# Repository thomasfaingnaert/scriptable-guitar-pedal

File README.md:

# A scriptable guitar pedal

## Building
### GNU/Linux (native compilation)
The following instructions are for Debian-based distributions.
Change the commands according to the distribution you are using.

1. Install the following prerequisites:
  - CMake
  - GNU Toolchain
  - Make
```bash
sudo apt-get update
sudo apt-get upgrade
sudo apt-get install cmake build-essential
```

2. Clone the repository and build the project:
```bash
git clone https://github.com/thomasfaingnaert/scriptable-guitar-pedal
mkdir build
cd build
cmake ../scriptable-guitar-pedal
make
```

3. Run the executable:
```bash
chmod +x ./scriptable-guitar-pedal
./scriptable-guitar-pedal
```

### Windows (cross compilation)
1. Install the following prerequisites, and make sure they are in your PATH:
  - CMake (https://cmake.org/)
  - Beaglebone GNU Toolchain (http://gnutoolchains.com/beaglebone/)
  - NMake (included in Visual Studio or Microsoft Visual C++ Build Tools)
  - PuTTY (https://www.putty.org/)

2. Clone the repository and build the project:
```powershell
git clone https://github.com/thomasfaingnaert/scriptable-guitar-pedal
mkdir build
cd build
cmake -G"NMake Makefiles" -DCMAKE_TOOLCHAIN_FILE="../scriptable-guitar-pedal/cmake/Toolchain.cmake" ../scriptable-guitar-pedal
nmake
```

### GNU/Linux (cross compilation)
1. Install the following prerequisites:
  - CMake
  - GNU Toolchain for ARM
  - Make

If you are using Ubuntu or one of its derivatives:
```bash
sudo apt install make cmake binutils-arm-linux-gnueabihf gcc-arm-linux-gnueabihf g++-arm-linux-gnueabihf
```

If you are using Fedora:
```bash
sudo dnf copr enable lantw44/arm-linux-gnueabihf-toolchain
sudo dnf install make cmake arm-linux-gnueabihf-{binutils,gcc,glibc}
```

Otherwise, change the commands according to the distribution you are using.

2. Clone the repository and build the project:
```bash
git clone https://github.com/thomasfaingnaert/scriptable-guitar-pedal
mkdir build
cd build
cmake -DCMAKE_TOOLCHAIN_FILE="../scriptable-guitar-pedal/cmake/Toolchain.cmake" ../scriptable-guitar-pedal
make
```

## Configuring the PRU
These instructions are for the Beaglebone image [Debian 9.3 2018-03-05 4GB SD IoT](http://debian.beagleboard.org/images/bone-debian-9.3-iot-armhf-2018-03-05-4gb.img.xz).
They may or may not work for you if you use a different one.

1. Make sure you can access the internet on the BeagleBone Black.
This can be done by configuring your internet adapter on your PC to share its connection with the Beaglebone.
Create a script `internet.sh` with the following contents:
```bash
#!/usr/bin/env bash
route add default gw 192.168.7.1
echo "nameserver 8.8.8.8" >> /etc/resolv.conf
```
Finally, run the script with sudo:
```bash
chmod +x ./internet.sh
sudo ./internet.sh
```

2. Update all packages:
```bash
sudo apt update
sudo apt upgrade
```

3. Delete RoboticsCape, as it blacklists the `uio_pruss` module
```bash
sudo apt purge roboticscape
```

4. Apply the Xenomai patches to the kernel using:
```bash
cd /opt/scripts/tools/
git pull
sudo ./update_kernel.sh --ti-xenomai-kernel --lts-4_9
sudo reboot
```
Finally, you can check if you are running the right kernel using:
```bash
uname -a
```
This should output something similar to `Linux beaglebone 4.9.88-ti-xenomai-r107 #1 SMP PREEMPT Sat Mar 24 09:29:27 UTC 2018 armv7l GNU/Linux`.

5. Next, we need to install our custom overlay:
```bash
cd device-tree/
make
sudo make install
```

6. Enable it by copying `uEnv-pru.txt` to the `boot/` folder:
```bash
cd boot/
sudo cp uEnv-pru.txt /boot/uEnv.txt
```

7. The UIO driver should now be loaded. You can verify this by running:
```bash
lsmod | grep uio
ls /dev/uio*
```

8. If you want to assemble PRU Assembly files on your PC, you should install the PRU assembler from https://github.com/beagleboard/am335x_pru_package.
Otherwise, you could copy the `*.p` files to the BBB using SCP and assemble them there.
To assemble a file `test.p`, you can use:
```bash
pasm -b test.p
```

9. Install the RTDM kernel module from https://github.com/thomasfaingnaert/rtdm_pruss_irq:
```bash
wget https://github.com/thomasfaingnaert/rtdm_pruss_irq/releases/download/v1.0/rtdm_pruss_irq.ko
sudo cp rtdm_pruss_irq.ko /lib/modules/`uname -r`/extra
sudo depmod -a
sudo modprobe rtdm_pruss_irq
```

10. Run the PRU loader to execute the PRU code:
```bash
./scriptable-guitar-pedal test.bin
```

## Building the ASoC codec driver

### GNU/Linux - Fedora (cross compilation)
These instructions are for Fedora based distributions.
Change the commands according to the distribution you are using.

1. Clone the official BeagleBoard and BeagleBone kernel repository and checkout the version the BeagleBone is running:
```bash
git clone https://github.com/beagleboard/linux
cd linux
git checkout 4.9.82-ti-r102
```

2. Make sure you have no stale .o files and dependencies lying around:
```bash
make mrproper
```

3. Modularize the ASoC codec driver:
```bash
mkdir ../build
make O=../build ARCH=arm bb.org_defconfig
make O=../build ARCH=arm menuconfig
```
Navigate to `Device Drivers/Sound Card Support/Advanced Linux Sound Architecture/ALSA for SoC audio support/CODEC drivers`
and modularize Cirrus Logic CS4271 CODEC (I2C).

4. Compile the kernel:
```bash
make O=../build ARCH=arm CROSS_COMPILE=arm-linux-gnueabihf-
```

5. Copy the modules on your to the BeagleBone Black:
```bash
scp ../build/sound/soc/codecs/snd-soc-cs4271-i2c.ko ../build/sound/soc/codecs/snd-soc-cs4271.ko debian@beaglebone.local:~
```

6. Install the modules on the BeagleBone Black:
```bash
ssh debian@beaglebone.local
sudo mv snd-soc-cs4271-i2c.ko snd-soc-cs4271.ko /lib/modules/4.9.82-ti-r102/extra/
sudo depmod -a
```

## Transferring to BeagleBone Black
To transfer the executable to your BeagleBone Black, you can use SSH, e.g. using PSCP (PuTTY Secure Copy) on Windows or SCP (Secure Copy) on GNU/Linux:
1. Copy the executable on your computer to the BeagleBone Black:
```powershell
pscp scriptable-guitar-pedal debian@192.168.7.2:/home/debian/scriptable-guitar-pedal
```
If you are using scp, change `pscp` to `scp`.
Also make sure to change the username (`debian`), destination path (`/home/debian/scriptable-guitar-pedal`) and IP address (`192.168.7.2`) if required.

2. Log in to the BeagleBone Black using SSH, and run the application:
```bash
chmod +x ./scriptable-guitar-pedal
./scriptable-guitar-pedal
```

## Using a custom Ne10 installation
The repository already includes a version of Ne10 in `include/ne10` and `lib/libNE10.a`.
If you want to use a custom Ne10 installation, you have to set the CMake variables `NE10_INCLUDE_DIRS` and `NE10_LIBRARIES` to point to the Ne10 include directory and library file, respectively.
An example when cross compiling on Windows:
```powershell
cmake -G"NMake Makefiles" -DCMAKE_TOOLCHAIN_FILE="../scriptable-guitar-pedal/cmake/Toolchain.cmake" -DNE10_INCLUDE_DIRS="/path/to/ne10/inc" -DNE10_LIBRARIES="/path/to/ne10/build/modules/libNE10.a" ../scriptable-guitar-pedal
```

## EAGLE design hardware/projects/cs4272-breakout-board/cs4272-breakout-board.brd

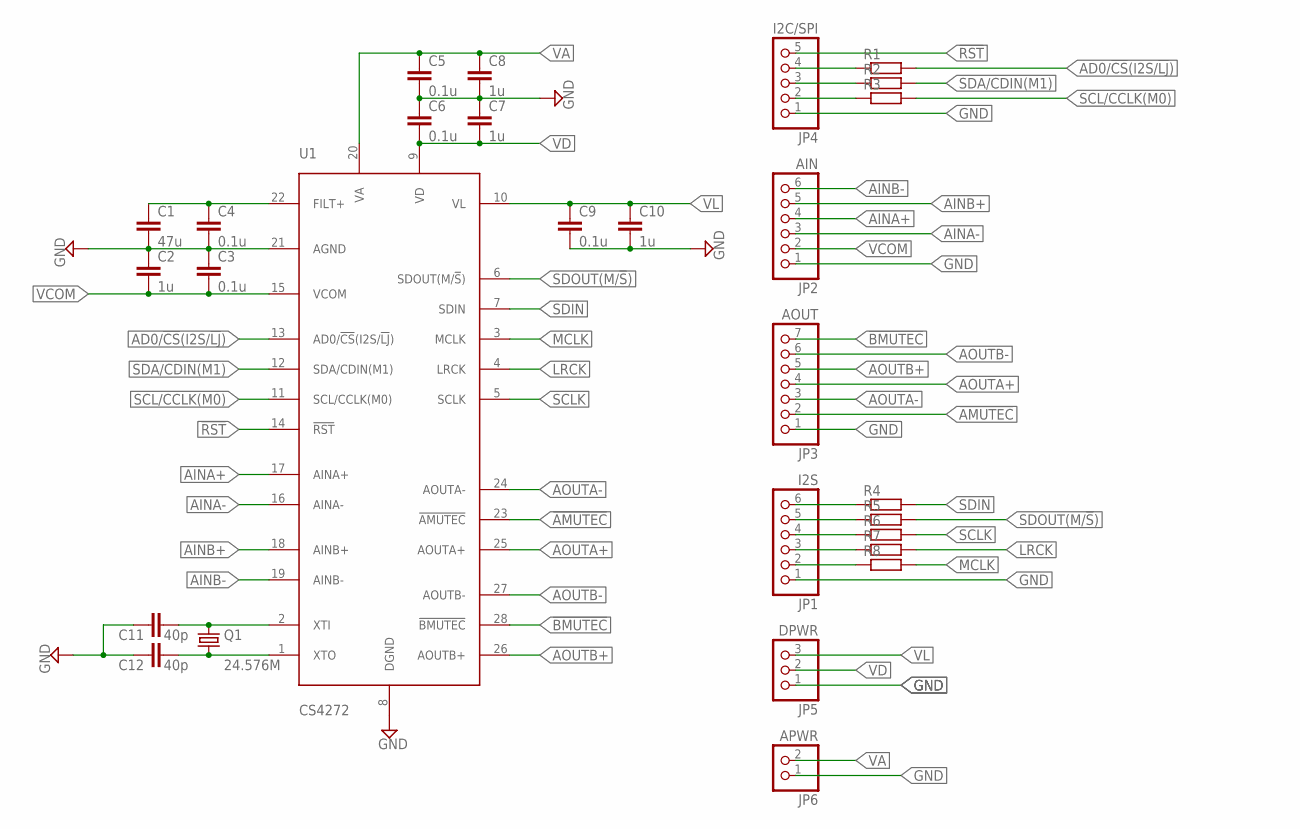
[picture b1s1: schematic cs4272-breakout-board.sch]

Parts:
C1: 47u; C0603
C2, C7, C8, C10: 1u; C0603
C3, C4, C5, C6, C9: 0.1u; C0603
C11, C12: 40p; C0603
JP1: I2S; 1X06
JP2: AIN; 1X06
JP3: AOUT; 1X07
JP4: I2C/SPI; 1X05
JP5: DPWR; 1X03
JP6: APWR; 1X02
Q1: 24.576M; HC49/S
R1, R2, R3, R4, R5, R6, R7, R8: R-EU_R0603; R0603
U1: CS4272; SOP65P640X120-28

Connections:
!AMUTEC!: JP3.2, U1.23 (!AMUTEC!)
!BMUTEC!: JP3.7, U1.28 (!BMUTEC!)
!RST!: JP4.5, U1.14 (!RST!)
AD0/!CS!(I2S/!LJ!): R1.2, U1.13 (AD0/!CS!(I2S/!LJ!))
AINA+: JP2.4, U1.17 (AINA+)
AINA-: JP2.3, U1.16 (AINA-)
AINB+: JP2.5, U1.18 (AINB+)
AINB-: JP2.6, U1.19 (AINB-)
AOUTA+: JP3.4, U1.25 (AOUTA+)
AOUTA-: JP3.3, U1.24 (AOUTA-)
AOUTB+: JP3.5, U1.26 (AOUTB+)
AOUTB-: JP3.6, U1.27 (AOUTB-)
FILT+: C1.1, C4.1, U1.22 (FILT+)
GND: C1.2, C2.1, C3.1, C4.2, C5.2, C6.1, C7.1, C8.2, C9.2, C10.2, C11.1, C12.1, JP1.1, JP2.1, JP3.1, JP4.1, JP5.1, JP6.1, U1.8 (DGND), U1.21 (AGND)
LRCK: R7.2, U1.4 (LRCK)
MCLK: R8.2, U1.3 (MCLK)
unnamed: JP4.4, R1.1
unnamed: JP4.3, R2.1
unnamed: JP4.2, R3.1
unnamed: JP1.2, R8.1
unnamed: JP1.3, R7.1
unnamed: JP1.4, R6.1
unnamed: JP1.5, R5.1
unnamed: JP1.6, R4.1
SCL/CCLK(M0): R3.2, U1.11 (SCL/CCLK(M0))
SCLK: R6.2, U1.5 (SCLK)
SDA/CDIN(M1): R2.2, U1.12 (SDA/CDIN(M1))
SDIN: R4.2, U1.7 (SDIN)
SDOUT(M/!S!): R5.2, U1.6 (SDOUT(M/!S!))
VA: C5.1, C8.1, JP6.2, U1.20 (VA)
VCOM: C2.2, C3.2, JP2.2, U1.15 (VCOM)
VD: C6.2, C7.2, JP5.2, U1.9 (VD)
VL: C9.1, C10.1, JP5.3, U1.10 (VL)
XTI: C11.2, Q1.2, U1.2 (XTI)
XTO: C12.2, Q1.1, U1.1 (XTO)

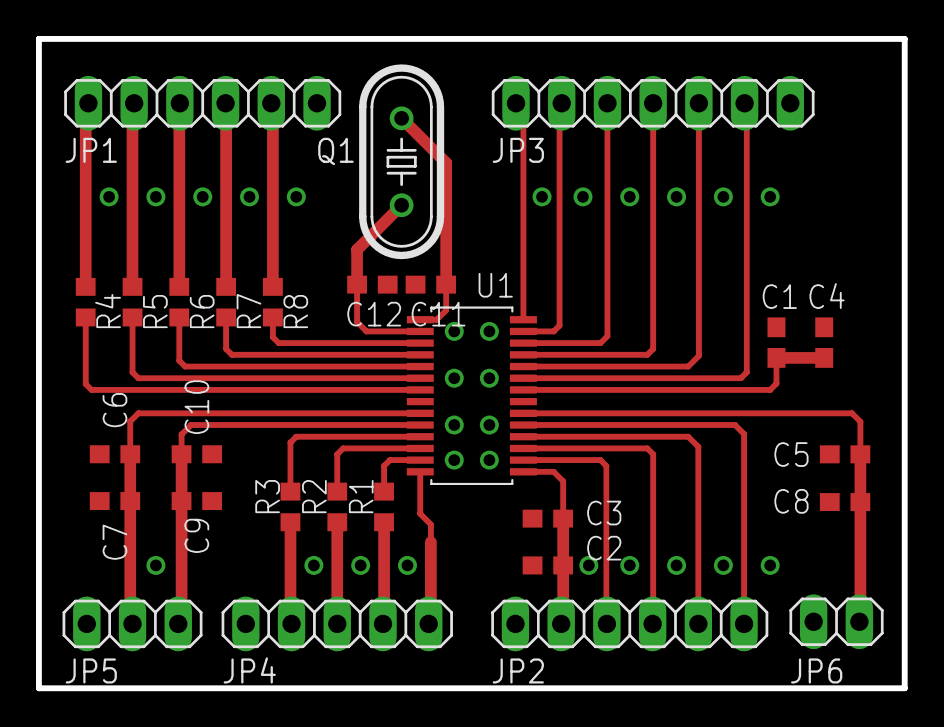
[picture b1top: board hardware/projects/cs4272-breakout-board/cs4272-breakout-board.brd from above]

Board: 2 copper layers, 48.1 x 36.1 mm, 28 parts (0 on the bottom side), 35 nets.

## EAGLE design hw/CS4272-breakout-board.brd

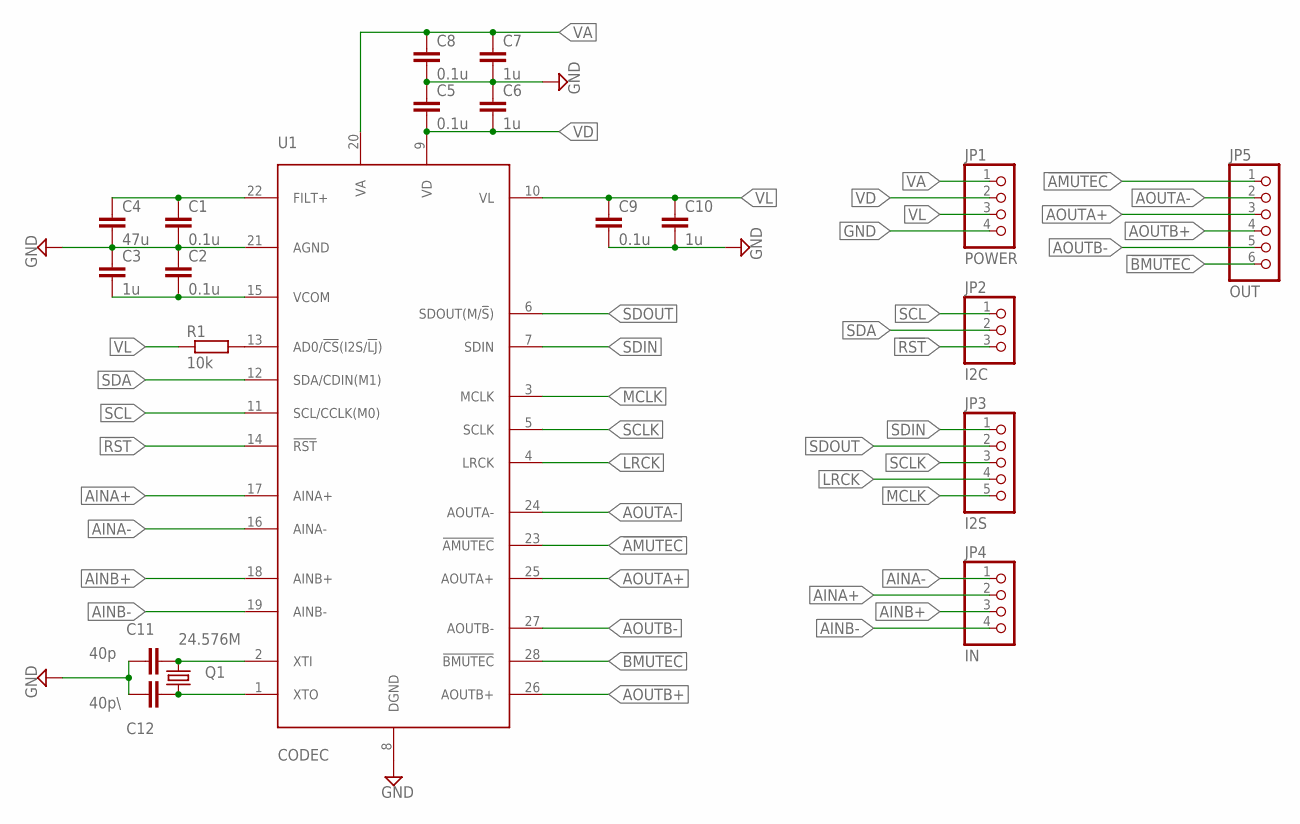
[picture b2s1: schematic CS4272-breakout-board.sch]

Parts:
C1, C2, C5, C8, C9: 0.1u; C0603
C3, C6, C7, C10: 1u; C0603
C4: 47u; C0603
C11: 40p; C0603
C12: 40p\; C0603
JP1: POWER; 1X04
JP2: I2C; 1X03
JP3: I2S; 1X05
JP4: IN; 1X04
JP5: OUT; 1X06
Q1: 24.576M; HC49U-V
R1: 10k; R0603
U1: CODEC; TSSOP-28

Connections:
!AMUTEC!: JP5.1, U1.23 (!AMUTEC!)
!BMUTEC!: JP5.6, U1.28 (!BMUTEC!)
!RST!: JP2.3, U1.14 (!RST!)
AINA+: JP4.2, U1.17 (AINA+)
AINA-: JP4.1, U1.16 (AINA-)
AINB+: JP4.3, U1.18 (AINB+)
AINB-: JP4.4, U1.19 (AINB-)
AOUTA+: JP5.3, U1.25 (AOUTA+)
AOUTA-: JP5.2, U1.24 (AOUTA-)
AOUTB+: JP5.4, U1.26 (AOUTB+)
AOUTB-: JP5.5, U1.27 (AOUTB-)
FILT+: C1.1, C4.1, U1.22 (FILT+)
GND: C1.2, C2.1, C3.1, C4.2, C5.1, C6.1, C7.2, C8.2, C9.2, C10.2, C11.1, C12.1, JP1.4, U1.8 (DGND), U1.21 (AGND)
LRCK: JP3.4, U1.4 (LRCK)
MCLK: JP3.5, U1.3 (MCLK)
unnamed: C12.2, Q1.1, U1.1 (XTO)
unnamed: C11.2, Q1.2, U1.2 (XTI)
unnamed: R1.2, U1.13 (AD0/!CS!(I2S/!LJ!))
SCL: JP2.1, U1.11 (SCL/CCLK(M0))
SCLK: JP3.3, U1.5 (SCLK)
SDA: JP2.2, U1.12 (SDA/CDIN(M1))
SDIN: JP3.1, U1.7 (SDIN)
SDOUT: JP3.2, U1.6 (SDOUT(M/!S!))
VA: C7.1, C8.1, JP1.1, U1.20 (VA)
VCOM: C2.2, C3.2, U1.15 (VCOM)
VD: C5.2, C6.2, JP1.2, U1.9 (VD)
VL: C9.1, C10.1, JP1.3, R1.1, U1.10 (VL)

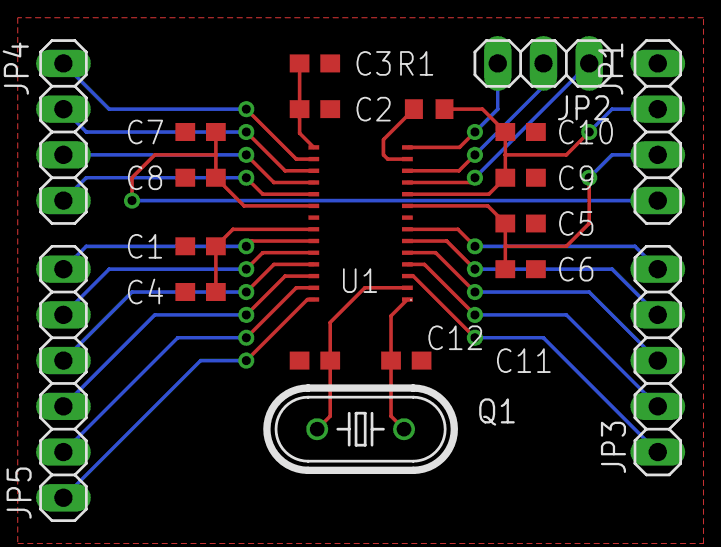
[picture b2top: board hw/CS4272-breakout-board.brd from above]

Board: 2 copper layers, 20 parts (0 on the bottom side), 27 nets.

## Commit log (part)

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2018-02-13 Add extra safety measure for parameters
2018-02-13 Add combfiltertest
2018-02-15 Add reverb with test
2018-02-19 Add basic project and Ne10 test
2018-02-19 Add README with build instructions for Windows
2018-02-19 Fix spacing and casing subtitles in README
2018-02-19 Add compilation instructions for GNU/Linux (native)
2018-02-19 Change minimum version CMake to 3.7
2018-02-19 Add cross compilation instructions for Fedora
2018-02-20 Add freeverb implementation
2018-02-20 Adjust reverb
2018-02-22 Add Civetweb test
2018-02-22 Move effects and samples to separate directory
2018-02-22 Add gitignore
2018-02-22 Move headers to appropriate directory
2018-02-22 Add device tree overlay
2018-02-22 Add I2C boilerplate
2018-02-23 Fix linking error to libi2c
    Closes #1
2018-02-23 Clean up main
2018-02-23 Implement exit URL
2018-02-23 Map exit command to /exit URL
2018-02-23 Implement file upload
2018-02-27 Add distortion effect with asymmetric clipping
2018-02-27 Add another asymmetric version of distortion
2018-02-27 Add another implementation of asymmetric distortion
2018-02-27 Revise distortiontest script
2018-02-27 Add minor changes to test scripts
2018-02-28 Update device tree
2018-03-01 Add device tree overlay build script
2018-03-01 Remove compiled device tree overlay
2018-03-01 Extend build command
2018-03-01 Add equalizer
2018-03-01 Implement audio file read and write
2018-03-02 Implement convolution
2018-03-02 Change parameters of distortion and equalizer
2018-03-03 Use FFT in overlap save algorithm
2018-03-03 Implement FilterEffect response setters
    Add setters for both frequency response and impulse response.
2018-03-03 Implement overlap save algorithm
2018-03-04 Add web interface to convolution effect
2018-03-04 Add various improvements
2018-03-04 Add performance logging to webserver
2018-03-05 Add visualisations
2018-03-05 Add breakout board
2018-03-10 Implement samplebuffer
2018-03-10 Implement basic version of sources and sinks
2018-03-10 Add sink tied to std::ostream
2018-03-10 Fix processor not working with out-of-sync sources
2018-03-10 Revert "Fix processor not working with out-of-sync sources"
    This reverts commit 471441696a233353490747be03069827129c2b5d.
2018-03-10 Disallow changing block size
2018-03-10 Add profiling code
2018-03-10 Implement filesource and filesink
2018-03-10 Optimise sinesource
2018-03-11 Implement tremolo effect
2018-03-11 Implement distortion effect
2018-03-11 Test multiple delays
2018-03-11 Add profiling code for FFT
2018-03-11 Revert "Add profiling code for FFT"
    This reverts commit 608e1569d170db294659e5273c0fe7b4f5bd7c20.
2018-03-12 Adjust tremolotest
2018-03-12 Avoid copies in FFT Convolver
2018-03-12 Add definition source block size
2018-03-12 Add I2C boilerplate code
2018-03-13 Update I2C interface
2018-03-13 Implement writeRegister()
2018-03-13 Refactor writeRegister() and add readRegister()
2018-03-13 Implement updateRegister()
2018-03-13 Add getters
2018-03-13 Begin rewriting convolver for larger blocksizes
2018-03-15 General makeover
2018-03-15 Add placeholder classes
2018-03-16 Add Travis CI configuration
2018-03-16 Add Travis status image to README
2018-03-16 Update device tree overlays
2018-03-17 Add TinyALSA
2018-03-17 Add distortion interface
2018-03-17 Add driver installation instructions
2018-03-17 Update instructions to fix symvers warning when probing the module
2018-03-18 Fix POST data handling
2018-03-18 Update device tree overlay
2018-03-18 Fix EOF
2018-03-18 Fix naming
2018-03-19 Add distortion handling
    Close #2
2018-03-20 Add delay interface
2018-03-20 Change interface for distortion
2018-03-20 Add a comment
2018-03-20 Add tremolo effect handling
2018-03-20 Add back links
2018-03-21 Update breakout board
2018-03-21 Remove trace
2018-03-21 Add gpio-of-helper
2018-03-22 Add libraries
2018-03-22 Change navbar
2018-03-23 Add effect-boxes to jsplumb div
2018-03-24 Add jsplumb endpoints to generated boxes
2018-03-26 Add compilation instructions for Ubuntu to README
2018-03-29 Implement basic Lua testing
2018-03-29 Implement calling C functions from Lua
2018-03-30 Add parameter info to effect boxes
2018-03-30 Add removed map files
2018-03-30 Add updated parameters in change-effect.js
2018-04-04 Add json parsing for effects with parameters
2018-04-04 Add changing effect functionality
2018-04-10 Add handler for chaining
2018-04-10 Add chaining effects processing
2018-04-10 Implement Lua effects
2018-04-10 Remove deprecated convolution code
2018-04-11 Remove unnecessary output from main
2018-04-11 Add profiling code for convolvers
2018-04-11 Add timing code for FFT Convolver
2018-04-11 Test convolution with sound samples
2018-04-11 Fix forgotten include in fftconvolver.cpp
2018-04-11 Add output to main thread
2018-04-11 Test Round-Robin scheduling
2018-04-12 Add AlsaSink
2018-04-13 Simulate AlsaSource
2018-04-13 Test non-uniform filter effect
2018-04-13 Improve testing code FilterEffect
2018-04-13 Implement custom impulse responses in FilterEffect
2018-04-13 Finish first implementation of FilterEffect
2018-04-13 Optimise FilterEffect 1: addition with Neon
2018-04-13 Optimise FilterEffect 2: use deque for buffering
2018-04-13 Add timing code per process call
2018-04-13 Revert "Add first version of multi-threaded filtereffect"
    This reverts commit 0d7d93233448671eb1c3c271a3a3e76e0f462d63.
2018-04-13 Revert "Revert "Add first version of multi-threaded filtereffect""
    This reverts commit a2e37236f4b797a65adfd8b66efcb9e583c65c10.
2018-04-13 Revert "Try adding prioritites in FilterEffect"
    This reverts commit d1e0810487669c26ab5c30da1566353627f95c8c.
2018-04-13 Revert "Revert "Revert "Add first version of multi-threaded filtereffect"""
    This reverts commit 1a4d17dd755e193daa15bef5d77f2111330f6951.
2018-04-13 Remove profiling code for each process call
2018-04-14 Fix upperbound in LuaEffect for loop
2018-04-14 Implement Lua distortion example
2018-04-14 Clean up FilterEffect
2018-04-14 Fix build error
2018-04-14 Cleanup
2018-04-16 Fix warnings
2018-04-16 Disable some warnings
2018-04-16 Use unsigned loop counters in LuaEffect
2018-04-16 Update samplerate
2018-04-17 Add lua interface
2018-04-17 Add samplerate option to filesink ctor
2018-04-17 Remove hardcoded samplerates from webserver
2018-04-18 Update reverb interface
2018-04-19 Remove obsoleted files
2018-04-19 Remove processor
2018-04-19 Add new version Source and Sink
2018-04-19 Reimplement SineSource using new API
2018-04-19 Reimplement FileSink using new API
2018-04-19 Adjust FileSource to work with new API
2018-04-19 Remove I2SDevice from CMakeLists
2018-04-19 Adjust TremoloEffect to work with new API
2018-04-19 Adjust LuaEffect to work with new API
2018-04-19 Adjust AlsaDevice to work with new API
2018-04-20 Adjust FilterEffect to work with new API
2018-04-21 Adjust DelayEffect to work with new API
2018-04-21 Add dl library to FindLua.cmake
2018-04-21 Update webserver to work with new chaining API
2018-04-21 Add basic example to use PRU
2018-04-21 Add PRU *.bin files to gitignore
2018-04-22 Add example shared memory PRU and CPU
2018-04-22 Abstract PRU to class
2018-04-22 Change PRU example to use PRU class
2018-04-22 Update chain form handling
    Fix #4
2018-04-22 Reposition send button in modal
2018-04-22 Update uEnv
2018-04-22 Fix compile features
2018-04-22 Add Xenomai userspace libraries (crosscompile)
2018-04-23 Add chain save
2018-04-23 Reimplement PRU example
2018-04-23 Use RTDM to wait for PRU interrupt
2018-04-23 Use correct interrupts for RTDM
2018-04-23 Measure latency in loop
2018-04-24 Improve saving chains
2018-04-24 Add load chain
2018-04-24 Unroll loop of multiplyComplex
2018-04-25 Fix filename Arm NEON complex library
2018-04-26 Add Loading chains
2018-04-27 Remove unnecessary line ending in license
2018-04-27 Update LICENSE
2018-04-28 Fix various UI bugs
2018-04-28 Reposition added effects
2018-04-28 Implement first version of FDL
2018-04-28 Add current chain save
2018-04-28 Add extra padding elements to frequency data
    Added extra elements to frequency data in FDL so that all complex arrays
    have sizes divisible by 8.
    This allows us to use the Neon SIMD extensions without having to worry
    about the 'leftover' elements should the size not be a multiple of 8.
2018-04-28 Improve output FDL test
2018-04-28 Fix opening modal on drag
2018-04-28 Print number of partitions in FDL test
2018-04-28 Move Xenomai license to third-party folder
2018-04-28 Remove FilterEffect
2018-04-28 Set priority of main thread
2018-04-29 Check if set priority succeeded
2018-04-29 Optimise filesink
2018-04-29 Fix various bugs and delete effect
2018-04-29 Make normalization in SampleData optional
2018-04-29 Add listing of impulse responses
2018-04-29 Change form handling on server side for conv
2018-04-29 Add base McASP code
2018-04-29 Add basic multithreading test in FilterEffect
2018-04-29 Remove unnecessary statement in FilterEffect
2018-04-29 Remove output in thread_function
2018-04-29 Initialise data before starting threads
2018-04-29 Reset inputAvailable flag when thread gets input
2018-04-29 Finish implementing scheduling in FilterEffect
2018-04-29 Optimise worker thread signalling
2018-04-30 Reorder synchronisation instructions in FilterEffect
2018-04-30 Determine initial counter values automatically
2018-04-30 Determine scheduling period automatically
2018-04-30 Set priority for each thread
2018-04-30 Rename base file
2018-04-30 Add base file
2018-04-30 Readd FDL testing code in main
2018-04-30 Convert FDL to non-template class
2018-04-30 Avoid setting outputFourier to zero in FDL
2018-04-30 Implement input for FilterEffect
2018-04-30 Implement basic input FilterEffect
2018-04-30 Add convolution test with one FDL
2018-04-30 Reorder locking output queue in thread_function
2018-04-30 Load impulseResponses via iterator
2018-04-30 Allow using multiple FDLs
2018-04-30 Set impulse response from main
2018-04-30 Add TODOs for possible optimisations
2018-04-30 Avoid dynamic allocation in thread_function
2018-05-01 Remove circularbuffer
2018-05-01 Remove unnecessary boost includes
2018-05-01 Use boost::circular_buffer for input buffering
2018-05-01 Partition impulse response in separate function
2018-05-01 Add Mode Control 1 write operations
2018-05-01 Fix abundant definitions
2018-05-01 Use pthread mutex for outputBuffer
2018-05-01 Fix typo
2018-05-01 Test version
2018-05-02 Refactor codec
2018-05-02 Add pru0 to exclusive-use, refactor PRU code, finish I2C initialization
2018-05-02 Remove excessive newline character
2018-05-02 Refactor alsa device tree
2018-05-02 Revert previous commit
2018-05-02 Use LJ instead of I2S
2018-05-02 Add documentation
2018-05-02 Fix error in ALSA device tree and expand PRU device tree
2018-05-02 Fix syntax error in PRU device tree
2018-05-03 Add no-idle to McASP0
2018-05-03 Refactor makefiles
2018-05-03 Add alsa handling
2018-05-04 Add multithreaded alsa handling
2018-05-04 Add Alsa handling in thread
2018-05-04 Add PruDevice to CMakeLists
2018-05-04 Fix alsa handle code errors
2018-05-05 Couldn't open PCM devices with refactored AlsaDevice
2018-05-05 Update device trees to use new kernel
2018-05-05 Add Makefile to pru/
2018-05-05 Fix AlsaDevice by initializing values to 0
2018-05-05 Rename
2018-05-05 Reorder installation instructions to not have problems with missing certificates during the kernel update
2018-05-05 Make code more readable
2018-05-05 Fix installation procedure order
2018-05-05 Add first register writes to McASP
2018-05-05 Add instructions to install RTDM driver
2018-05-05 Add write to AFSRCTL
2018-05-05 Add ram_input_push test
2018-05-05 Remove old PRU interrupt code
2018-05-05 Update PRU circular buffer size
2018-05-07 Fix typo, add ram to Makefile
2018-05-07 Adjust comment style
2018-05-07 Use consistent naming
2018-05-07 Set up source to write McASP code
2018-05-07 Remove excessive newline
2018-05-07 Do not use /dev/mem to read and write to shared RAM
2018-05-07 Do not check return code, as it cannot fail
2018-05-07 Add McASP initialization code
2018-05-11 Change reverb interface
2018-05-11 Add chain handling for convolution
2018-05-17 Fix missing include in webserver
2018-05-17 Fix warnings in webserver
2018-05-17 Use hexadecimal constants in codec
2018-05-17 Change alsa handling
2018-05-18 Fix conversion
2018-05-21 Fix mistake in html and update alsa
2018-05-21 Remove console.logs
2018-05-21 Make alsa + web server work
